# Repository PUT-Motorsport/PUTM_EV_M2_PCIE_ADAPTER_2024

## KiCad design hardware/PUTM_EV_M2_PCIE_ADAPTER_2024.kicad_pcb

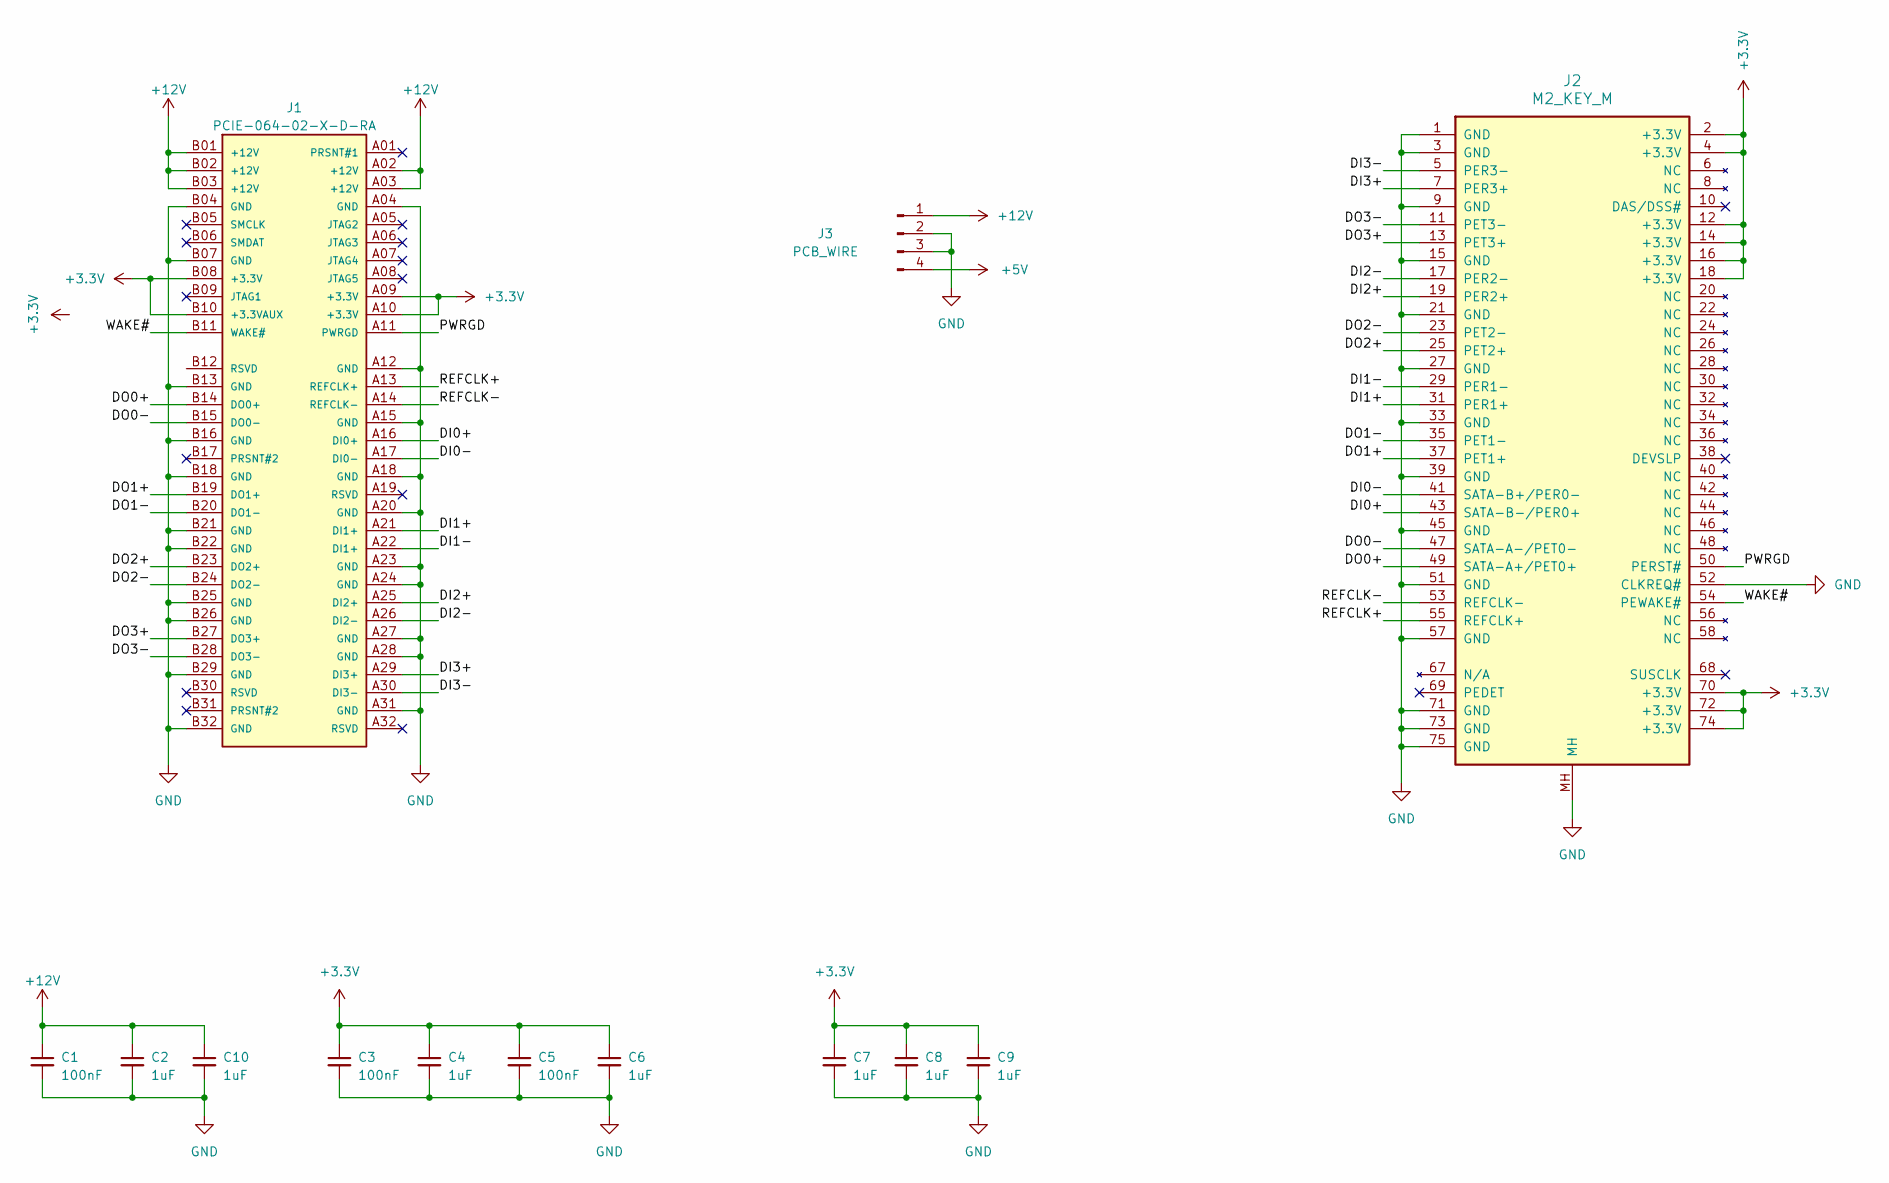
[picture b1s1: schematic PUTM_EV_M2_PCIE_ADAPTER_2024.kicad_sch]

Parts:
C1, C3, C5: 100nF; C_0402_1005Metric
C2, C4, C6, C7, C8, C9, C10: 1uF; C_0603_1608Metric
J1: PCIE-064-02-X-D-RA; SAMTEC_PCIE-064-02-X-D-RA; PARTREV D
J2: M2_KEY_M; M.2-KEY-M-FAT
J3: PCB_WIRE; SolderWire-0.1sqmm_1x04_P3.6mm_D0.4mm_OD1mm_Relief

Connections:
+3.3V: C3.1, C4.1, C5.1, C6.1, C7.1, C8.1, C9.1, J1.A09 (+3.3V), J1.A10 (+3.3V), J1.B08 (+3.3V), J1.B10 (+3.3VAUX), J2.2 (+3.3V), J2.4 (+3.3V), J2.12 (+3.3V), J2.14 (+3.3V), J2.16 (+3.3V), J2.18 (+3.3V), J2.70 (+3.3V), J2.72 (+3.3V), J2.74 (+3.3V)
+5V: J3.4
+12V: C1.1, C2.1, C10.1, J1.A02 (+12V), J1.A03 (+12V), J1.B01 (+12V), J1.B02 (+12V), J1.B03 (+12V), J3.1
/DI0+: J1.A16 (DI0+), J2.43 (SATA-B-/PER0+)
/DI0-: J1.A17 (DI0-), J2.41 (SATA-B+/PER0-)
/DI1+: J1.A21 (DI1+), J2.31 (PER1+)
/DI1-: J1.A22 (DI1+), J2.29 (PER1-)
/DI2+: J1.A25 (DI2+), J2.19 (PER2+)
/DI2-: J1.A26 (DI2-), J2.17 (PER2-)
/DI3+: J1.A29 (DI3+), J2.7 (PER3+)
/DI3-: J1.A30 (DI3-), J2.5 (PER3-)
/DO0+: J1.B14 (DO0+), J2.49 (SATA-A+/PET0+)
/DO0-: J1.B15 (DO0-), J2.47 (SATA-A-/PET0-)
/DO1+: J1.B19 (DO1+), J2.37 (PET1+)
/DO1-: J1.B20 (DO1-), J2.35 (PET1-)
/DO2+: J1.B23 (DO2+), J2.25 (PET2+)
/DO2-: J1.B24 (DO2-), J2.23 (PET2-)
/DO3+: J1.B27 (DO3+), J2.13 (PET3+)
/DO3-: J1.B28 (DO3-), J2.11 (PET3-)
/PWRGD: J1.A11 (PWRGD), J2.50 (PERST#)
/REFCLK+: J1.A13 (REFCLK+), J2.55 (REFCLK+)
/REFCLK-: J1.A14 (REFCLK-), J2.53 (REFCLK-)
/WAKE#: J1.B11 (WAKE#), J2.54 (PEWAKE#)
GND: C1.2, C2.2, C3.2, C4.2, C5.2, C6.2, C7.2, C8.2, C9.2, C10.2, J1.A04 (GND), J1.A12 (GND), J1.A15 (GND), J1.A18 (GND), J1.A20 (GND), J1.A23 (GND), J1.A24 (GND), J1.A27 (GND), J1.A28 (GND), J1.A31 (GND), J1.B04 (GND), J1.B07 (GND), J1.B13 (GND), J1.B16 (GND), J1.B18 (GND), J1.B21 (GND), J1.B22 (GND), J1.B25 (GND), J1.B26 (GND), J1.B29 (GND), J1.B32 (GND), J2.1 (GND), J2.3 (GND), J2.9 (GND), J2.15 (GND), J2.21 (GND), J2.27 (GND), J2.33 (GND), J2.39 (GND), J2.45 (GND), J2.51 (GND), J2.52 (CLKREQ#), J2.57 (GND), J2.71 (GND), J2.73 (GND), J2.75 (GND), J2.MH, J3.2, J3.3

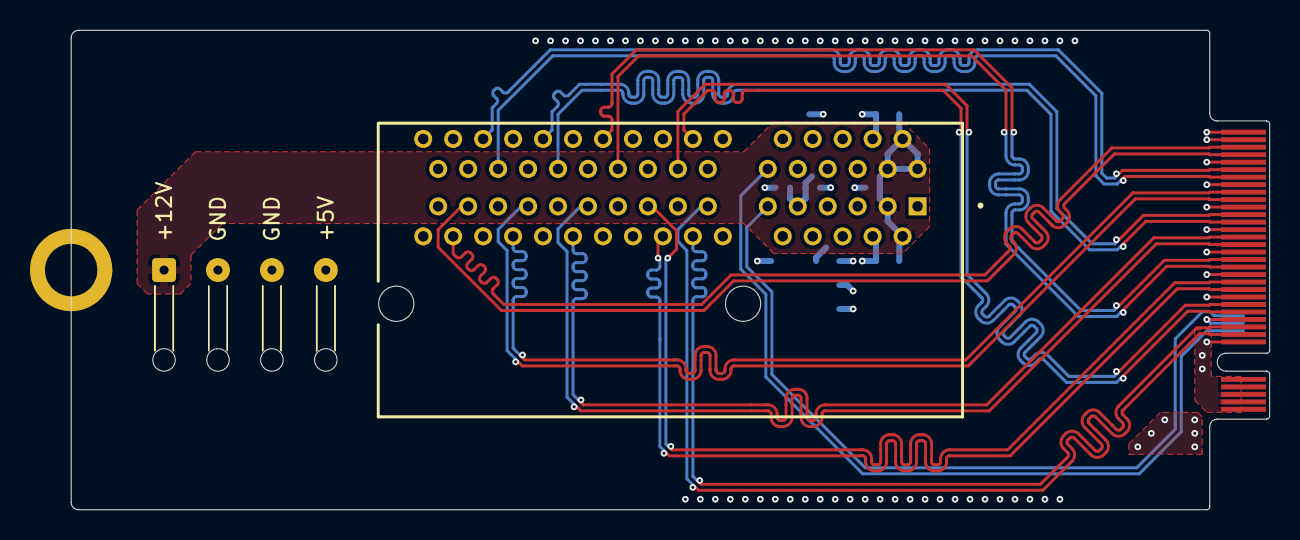
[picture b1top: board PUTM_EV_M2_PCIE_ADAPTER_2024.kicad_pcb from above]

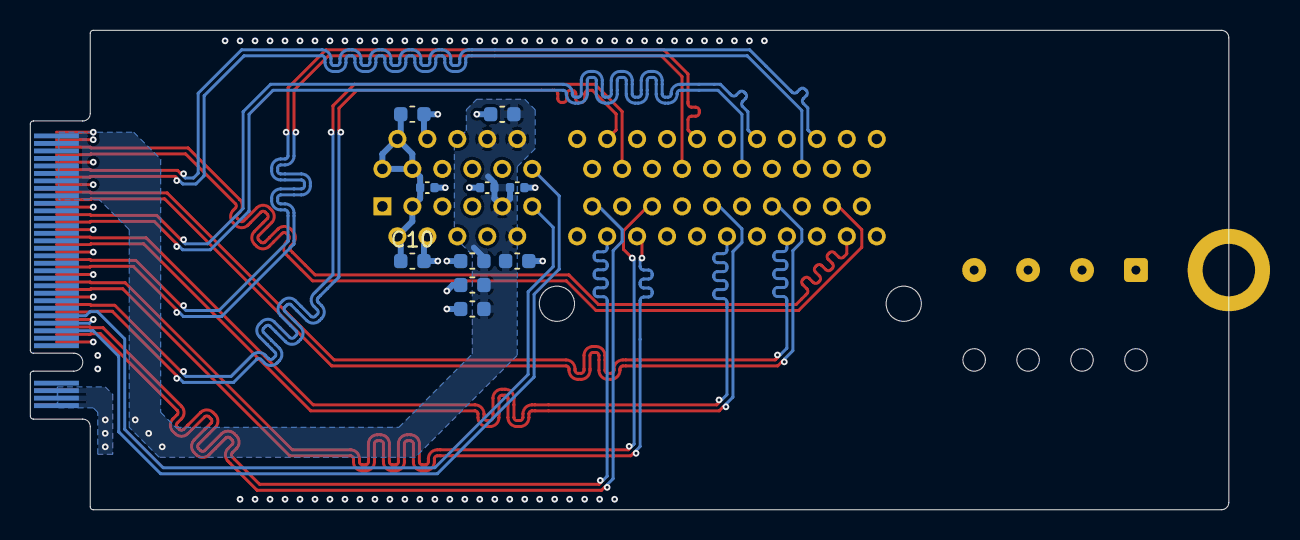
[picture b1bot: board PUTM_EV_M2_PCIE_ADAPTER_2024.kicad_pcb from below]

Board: 4 copper layers, 80.0 x 32.0 mm, 13 parts (11 on the bottom side), 23 nets.

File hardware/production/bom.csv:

Designator,Footprint,Quantity,Value,LCSC Part #
"C1, C3, C5",0402,3,100nF,
"C10, C2, C4, C6, C7, C8, C9",0603,7,1uF,
J1,SAMTEC_PCIE-064-02-X-D-RA,1,PCIE-064-02-X-D-RA,
J2,M.2-KEY-M-FAT,1,M2_KEY_M,
J3,SolderWire-0.1sqmm_1x04_P3.6mm_D0.4mm_OD1mm_Relief,1,PCB_WIRE,

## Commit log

2024-03-03 high speed signals routing done
2024-03-05 deleted all tracks, needs a bigger board
2024-03-20 final design
